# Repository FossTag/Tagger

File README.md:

Repurpose your old nerf-or-similar toy guns that were destined for the trash heap.
Rip their guts out, and replace them with this Open Hardware, Arduino based PCB, an infrared LED, a trigger switch, and optionally some LEDs and/or speakers for feedback.

Print the PCB yourself at a commercial fabrication shop, or hack together your own using a bit of stripboard using the relatively straightforward schematics.

## See also

* **[@FossTag](https://github.com/FossTag)** - for an overview of the broader project.
* **[@FossTag/TaggerFirmware](https://github.com/FossTag/TaggerFirmware)** - for the latest firmware for this PCB.

## PCB design

Currently, the PCB supports the following:
* Mounting an Arduino Pro Mini.
* Trigger button and IR LED for firing.
* RGB LED and speaker for audio/visual feedback.
* Battery input from a 9V or other appropriate battery.

For details of the latest and all past revisions, check out the [GitHub Releases](https://github.com/FossTag/Tagger/releases) page.
It will include a detailed description of each PCB revision, and also Kicad source files + some Gerber files for specific PCB manufacturers.

### Approx list of materials
* Old nerf gun (and some creativity)
* Arduino Pro Mini
    * 5V version if you wish to drive a piezo speaker for audio feedback
    * 3V otherwise
* 9V battery (or other power source that can connect to the Arduino Pro Mini raw voltage input pin)
* IR LED + resistor for firing
* Momentary switch for trigger
* Optional:
    * 2 x LEDs + resistors for visual feedback of firing and getting hit.
    * 1 x Piezo speaker for audio feedback of firing, getting hit, and dying.

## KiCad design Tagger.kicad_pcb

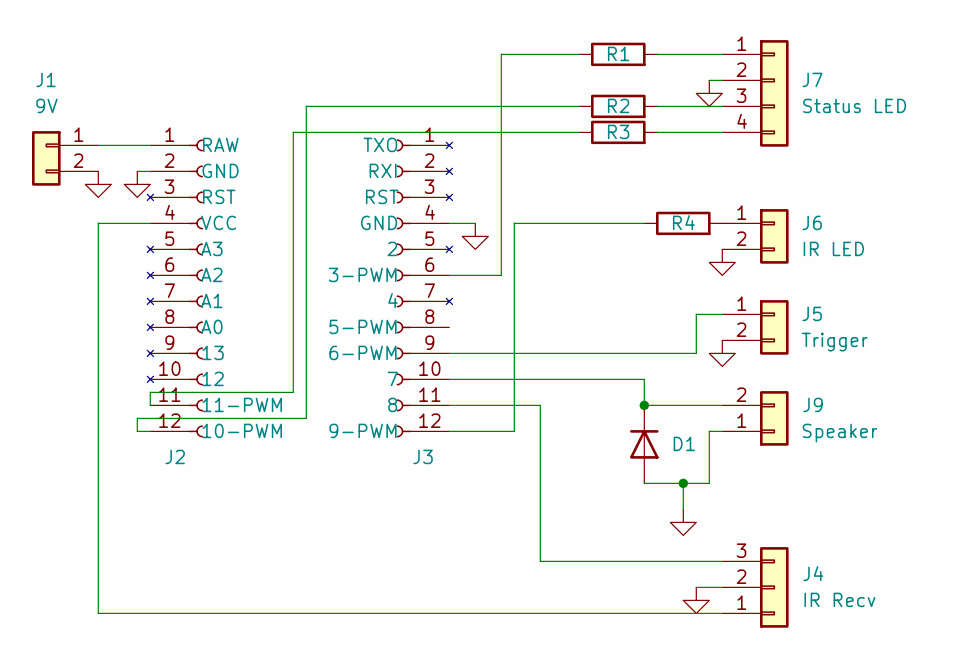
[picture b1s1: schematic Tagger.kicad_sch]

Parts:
D1: D; D_T-1_P10.16mm_Horizontal
J1: 9V; PinHeader_1x02_P2.54mm_Vertical
J2, J3: Conn_01x12_Female; PinSocket_1x12_P2.54mm_Vertical
J4: IR Recv; PinHeader_1x03_P2.54mm_Vertical
J5: Trigger; PinHeader_1x02_P2.54mm_Vertical
J6: IR LED; PinHeader_1x02_P2.54mm_Vertical
J7: Status LED; PinHeader_1x04_P2.54mm_Vertical
J9: Speaker; PinHeader_1x02_P2.54mm_Vertical
R1, R2, R3, R4: R; R_Axial_DIN0207_L6.3mm_D2.5mm_P10.16mm_Horizontal

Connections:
GND: D1.2 (A), J1.2, J2.2 (GND), J3.4 (GND), J4.2, J5.2, J6.2, J7.2, J9.1
unnamed: D1.1 (K), J3.10 (7), J9.2
unnamed: J1.1, J2.1 (RAW)
unnamed: J2.11 (11-PWM), R3.1
unnamed: J2.12 (10-PWM), R2.1
unnamed: J2.4 (VCC), J4.1
unnamed: J3.11 (8), J4.3
unnamed: J3.9 (6-PWM), J5.1
unnamed: J6.1, R4.2
unnamed: J3.6 (3-PWM), R1.1
unnamed: J7.1, R1.2
unnamed: J7.3, R2.2
unnamed: J7.4, R3.2
unnamed: J3.12 (9-PWM), R4.1

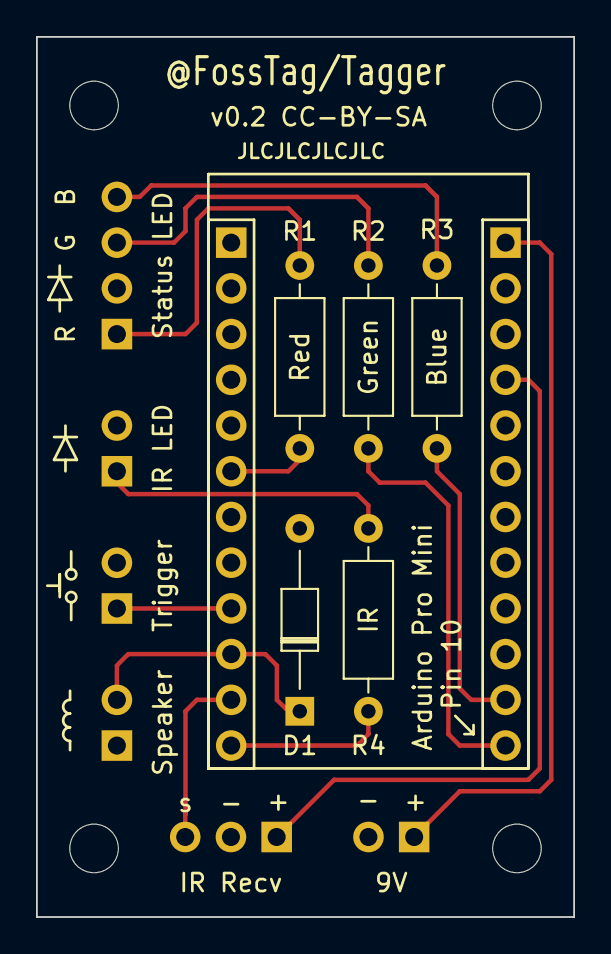
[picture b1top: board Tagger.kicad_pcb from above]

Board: 2 copper layers, 29.8 x 48.9 mm, 13 parts (0 on the bottom side), 14 nets.

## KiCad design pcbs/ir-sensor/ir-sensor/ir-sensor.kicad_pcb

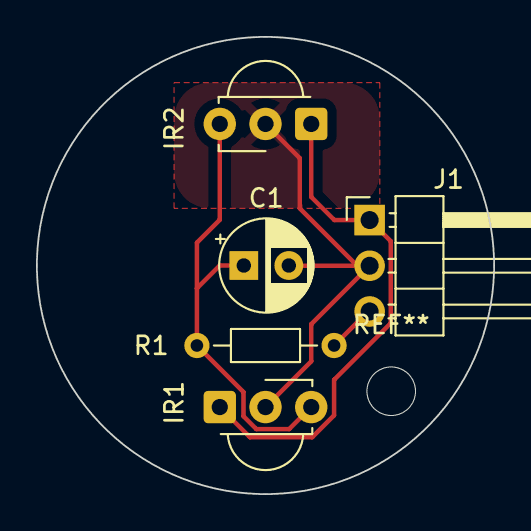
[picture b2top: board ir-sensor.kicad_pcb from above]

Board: 2 copper layers, 25.4 x 25.4 mm, 5 parts (0 on the bottom side), 4 nets.

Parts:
C1: 100; CP_Radial_D5.0mm_P2.50mm
IR1, IR2: TSOP38G36; Vishay_MINICAST-3Pin
J1: Conn_01x03_Male; PinHeader_1x03_P2.54mm_Horizontal
R1: 100; R_Axial_DIN0204_L3.6mm_D1.6mm_P7.62mm_Horizontal

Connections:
GND: C1.2, IR1.2 (GND), IR2.2 (GND), J1.2
unnamed: J1.3, R1.2
unnamed: IR1.1 (OUT), IR2.1 (OUT), J1.1
unnamed: C1.1, IR1.3 (Vs), IR2.3 (Vs), R1.1

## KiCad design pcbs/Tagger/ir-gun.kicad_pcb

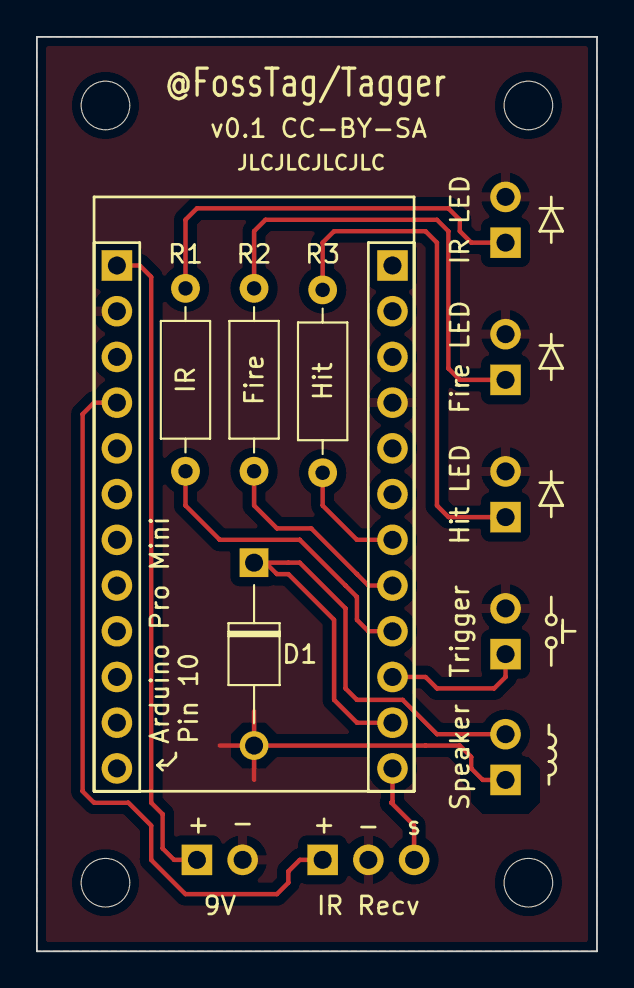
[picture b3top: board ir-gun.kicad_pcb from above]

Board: 2 copper layers, 31.1 x 50.8 mm, 13 parts (0 on the bottom side), 12 nets.

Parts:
D1: D; D_T-1_P10.16mm_Horizontal
J1: 9V; PinHeader_1x02_P2.54mm_Vertical
J2, J3: Conn_01x12_Female; PinSocket_1x12_P2.54mm_Vertical
J4: IR Recv; PinHeader_1x03_P2.54mm_Vertical
J5: Trigger; PinHeader_1x02_P2.54mm_Vertical
J6: IR LED; PinHeader_1x02_P2.54mm_Vertical
J7: Fire LED; PinHeader_1x02_P2.54mm_Vertical
J8: Hit LED; PinHeader_1x02_P2.54mm_Vertical
J9: Speaker; PinHeader_1x02_P2.54mm_Vertical
R1, R2, R3: R; R_Axial_DIN0207_L6.3mm_D2.5mm_P10.16mm_Horizontal

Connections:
GND: D1.2 (A), J1.2, J2.2 (GND), J3.4 (GND), J4.2, J5.2, J6.2, J7.2, J8.2, J9.1
unnamed: D1.1 (K), J3.11 (8), J9.2
unnamed: J1.1, J2.1 (RAW)
unnamed: J2.4 (VCC), J4.1
unnamed: J3.7 (4), R3.1
unnamed: J3.8 (5), R2.1
unnamed: J3.9 (6), R1.1
unnamed: J3.10 (7), J5.1
unnamed: J3.12 (9), J4.3
unnamed: J6.1, R1.2
unnamed: J7.1, R2.2
unnamed: J8.1, R3.2

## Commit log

2022-10-02 Initial sketch, including a fire button and a fire status LED.
2022-10-07 Add IR receiver with LED + speaker feedack when hit.
2022-10-08 Begin documenting, both via README, and also the serial monitor reporting back its configuration and desired hardware connections.
2022-11-01 Shuffle code down into the 'firmware' directory, so 'pcbs' can eventually live at the top level too.
2022-11-01 Add GPLv3.0 license.
2022-11-16 First revision of Tagger board.
    Designed to mount an Arduino Pro Mini 5v/16MHz board via header pins,
    as well as IR LED, IR sensor, Hit + Status LEDs, and a trigger button.
2022-11-16 Working on revision 2.
    Diode is not strangely routed to ground any more, it is more sensible and direct.
    Ground plane moved to the back so that it can print as a 2 sided board with the
    silk screen on top (currently it is a one sided one with silk screen on the back
    accidentally).
2022-11-16 Add license and skeleton readme with license badge.
2022-11-17 First moves towards v0.2 of the board.
    * Replace 2 x status LED's with a single RGB LED.
    * Dobule sided (ground plane on bottom).
    * Better routes for speaker diode.
2022-11-20 Flip mounted arduino so that it is correctly oriented when mounted on the front of the board.
    Involved moving all other headers mounts to the other side of the
    board so that it was easier to route. Also ensured we correctly
    use PWM pins for the RGB LED.
2022-11-20 Output gerber files to local directory.
    However, they are excluded from git right now, as we will eventually
    publish them as github releases.
2022-11-30 Add documentation to readme (including images).

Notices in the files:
README.md:
License: CC-BY-SA
Tagger.kicad_pcb:
v0.2 CC-BY-SA
pcbs/Tagger/ir-gun.kicad_pcb:
v0.1 CC-BY-SA
